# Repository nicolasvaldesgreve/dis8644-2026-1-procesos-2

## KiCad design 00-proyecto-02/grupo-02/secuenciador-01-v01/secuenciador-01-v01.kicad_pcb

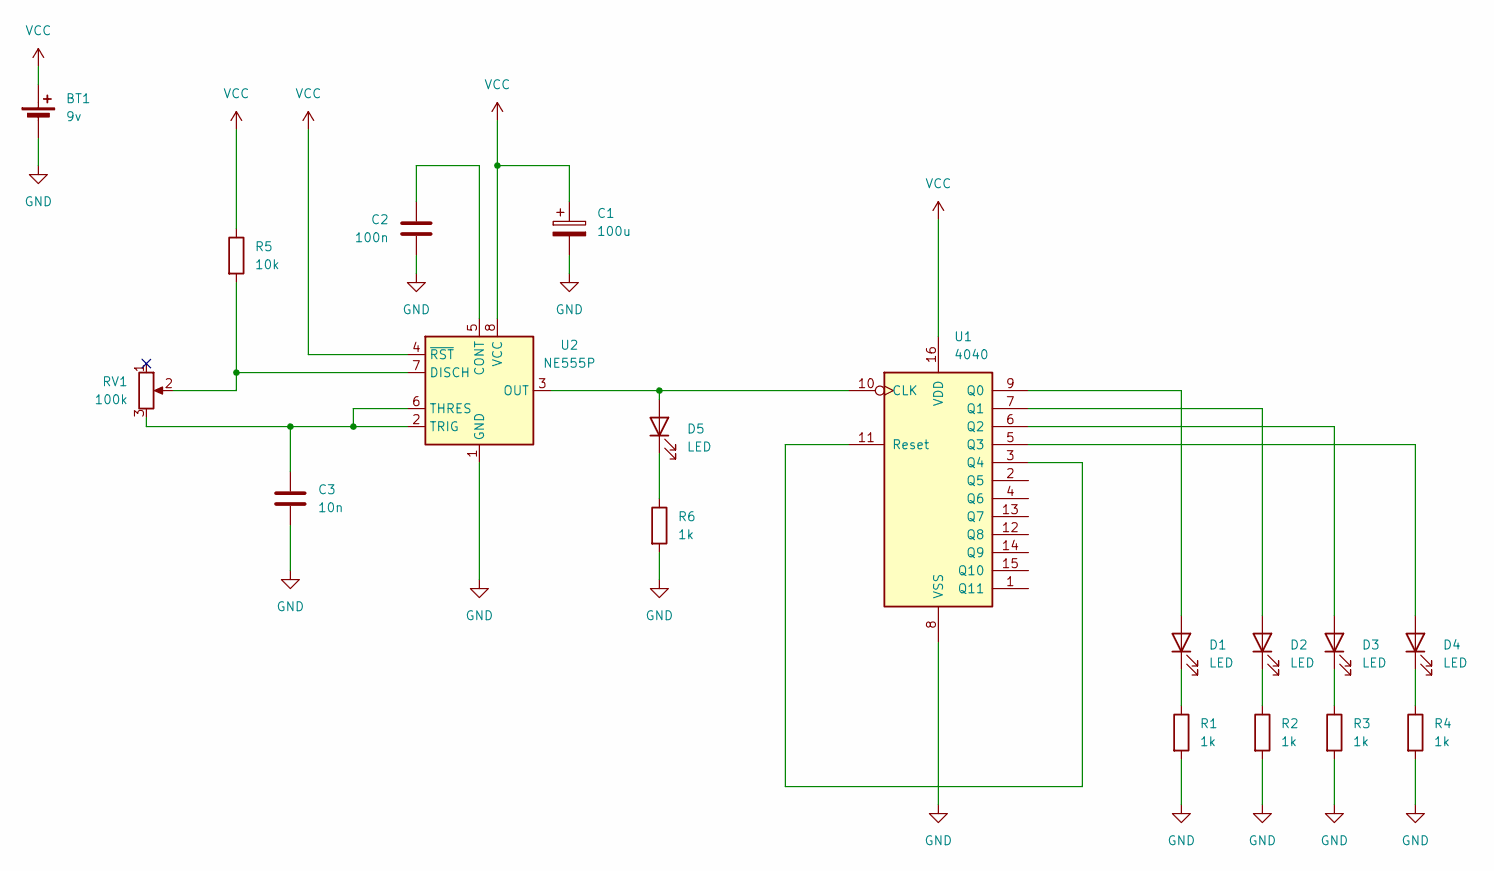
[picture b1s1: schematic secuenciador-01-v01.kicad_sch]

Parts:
BT1: 9v; TerminalBlock_MaiXu_MX126-5.0-02P_1x02_P5.00mm
C1: 100u; CP_Radial_D5.0mm_P2.50mm
C2: 100n; C_Disc_D3.8mm_W2.6mm_P2.50mm
C3: 10n; C_Disc_D3.8mm_W2.6mm_P2.50mm
D1, D2, D3, D4, D5: LED; LED_D5.0mm
R1, R2, R3, R4, R6: 1k; R_Axial_DIN0207_L6.3mm_D2.5mm_P10.16mm_Horizontal
R5: 10k; R_Axial_DIN0207_L6.3mm_D2.5mm_P10.16mm_Horizontal
RV1: 100k; Potentiometer_Alps_RK163_Single_Horizontal
U1: 4040; DIP-16_W7.62mm
U2: NE555P; DIP-8_W7.62mm

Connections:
GND: BT1.2 (-), C1.2, C2.2, C3.2, R1.2, R2.2, R3.2, R4.2, R6.2, U1.8 (VSS), U2.1 (GND)
unnamed: D1.2 (A), U1.9 (Q0)
unnamed: D1.1 (K), R1.1
unnamed: D2.2 (A), U1.7 (Q1)
unnamed: D2.1 (K), R2.1
unnamed: D3.2 (A), U1.6 (Q2)
unnamed: D3.1 (K), R3.1
unnamed: D4.2 (A), U1.5 (Q3)
unnamed: D4.1 (K), R4.1
unnamed: D5.2 (A), U1.10 (CLK), U2.3 (OUT)
unnamed: D5.1 (K), R6.1
unnamed: U1.3 (Q4), U1.11 (Reset)
unnamed: C2.1, U2.5 (CONT)
unnamed: R5.2, RV1.2, U2.7 (DISCH)
unnamed: C3.1, RV1.3, U2.2 (TRIG), U2.6 (THRES)
VCC: BT1.1 (+), C1.1, R5.1, U1.16 (VDD), U2.4 (~RST), U2.8 (VCC)

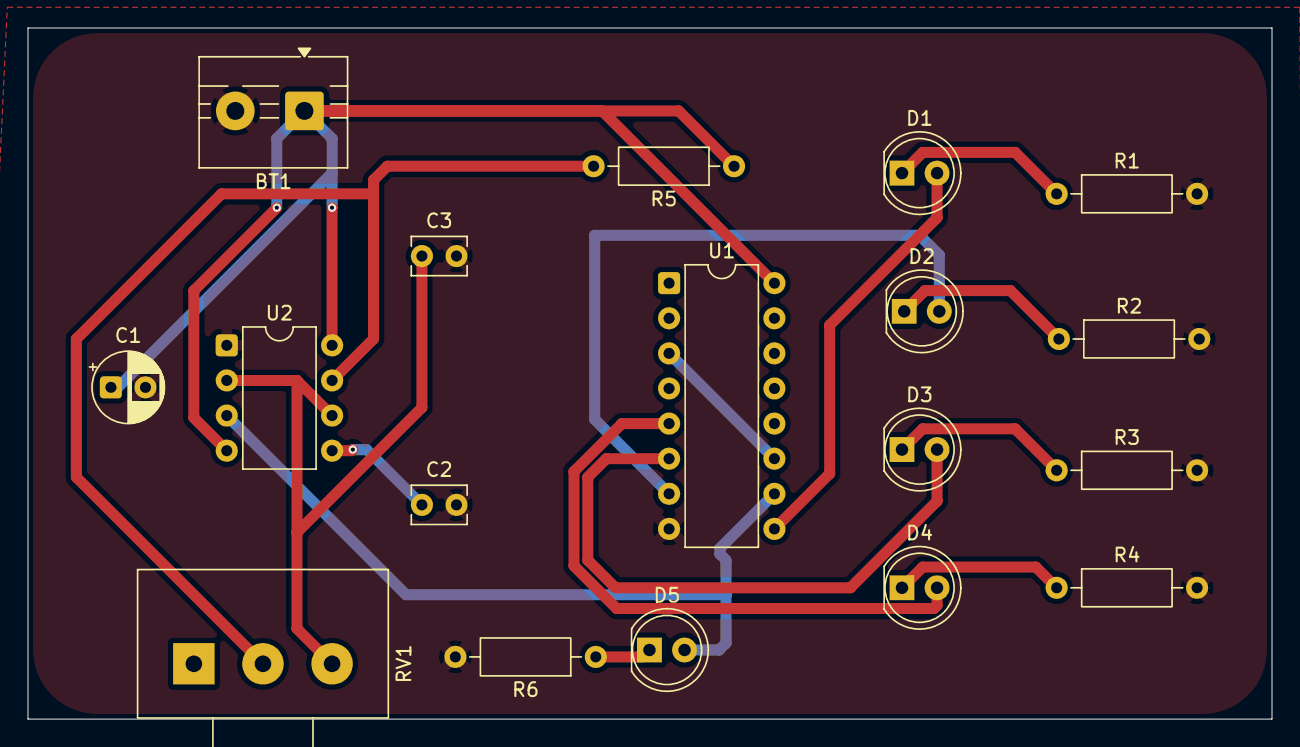
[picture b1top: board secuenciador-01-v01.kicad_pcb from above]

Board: 2 copper layers, 90.0 x 50.0 mm, 18 parts (0 on the bottom side), 16 nets.

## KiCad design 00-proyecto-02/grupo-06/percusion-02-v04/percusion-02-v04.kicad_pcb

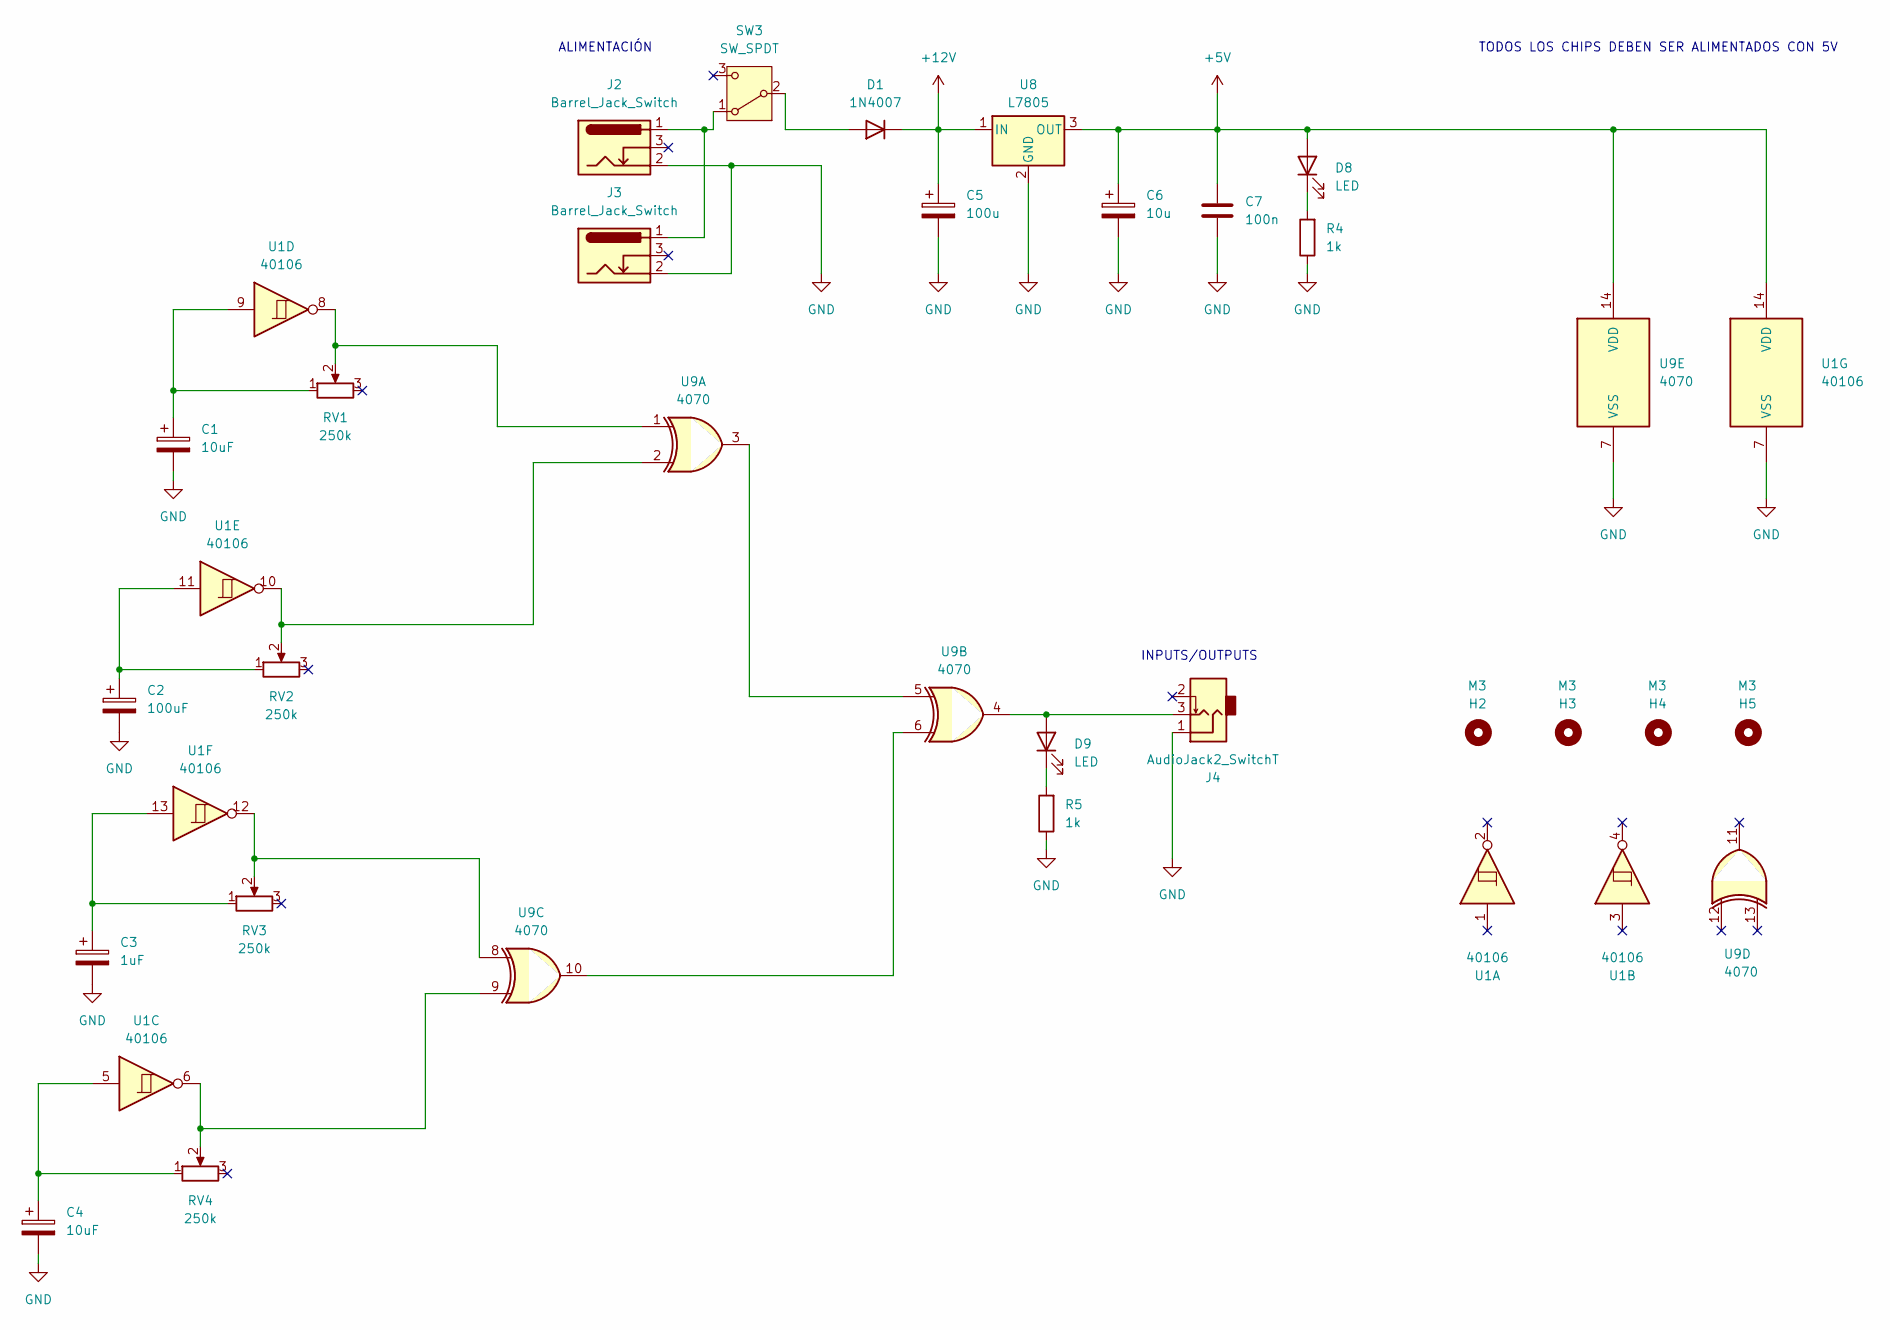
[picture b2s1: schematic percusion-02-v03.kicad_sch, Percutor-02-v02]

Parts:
C1, C4: 10uF; CP_Radial_D8.0mm_P3.80mm
C2: 100uF; CP_Radial_D8.0mm_P3.80mm
C3: 1uF; CP_Radial_D8.0mm_P3.80mm
C5: 100u; CP_Radial_D8.0mm_P3.80mm
C6: 10u; CP_Radial_D4.0mm_P2.00mm
C7: 100n; C_Disc_D5.0mm_W2.5mm_P2.50mm
D1: 1N4007; D_DO-41_SOD81_P10.16mm_Horizontal
D8, D9: LED; LED_D5.0mm
H2, H3, H4, H5: M3; MountingHole_3.2mm_M3
J2, J3: Barrel_Jack_Switch; BarrelJack_Horizontal
J4: AudioJack2_SwitchT; PJ301M-12
R4, R5: 1k; R_Axial_DIN0207_L6.3mm_D2.5mm_P10.16mm_Horizontal
RV1, RV2, RV3, RV4: 250k; Potentiometer_Alps_RK163_Single_Horizontal
SW3: SW_SPDT; spdt_ssd12d00g3
U1: 40106; DIP-14_W7.62mm_LongPads
U8: L7805; TO-220-3_Horizontal_TabDown
U9: 4070; DIP-14_W7.62mm_LongPads

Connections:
+5V: C6.1, C7.1, D8.2 (A), U1.14 (VDD), U8.3 (OUT), U9.14 (VDD)
+12V: C5.1, D1.1 (K), U8.1 (IN)
GND: C1.2, C2.2, C3.2, C4.2, C5.2, C6.2, C7.2, J2.2, J3.2, J4.1, R4.1, R5.1, U1.7 (VSS), U8.2 (GND), U9.7 (VSS)
unnamed: C1.1, RV1.1, U1.9
unnamed: C2.1, RV2.1, U1.11
unnamed: C3.1, RV3.1, U1.13
unnamed: C4.1, RV4.1, U1.5
unnamed: D1.2 (A), SW3.2 (B)
unnamed: D8.1 (K), R4.2
unnamed: D9.2 (A), J4.3, U9.4
unnamed: D9.1 (K), R5.2
unnamed: RV1.2, U1.8, U9.1
unnamed: RV2.2, U1.10, U9.2
unnamed: RV3.2, U1.12, U9.8
unnamed: RV4.2, U1.6, U9.9
unnamed: J2.1, J3.1, SW3.1 (A)
unnamed: U9.3, U9.5
unnamed: U9.6, U9.10

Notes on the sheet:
TODOS LOS CHIPS DEBEN SER ALIMENTADOS CON 5V
ALIMENTACIÓN
INPUTS/OUTPUTS

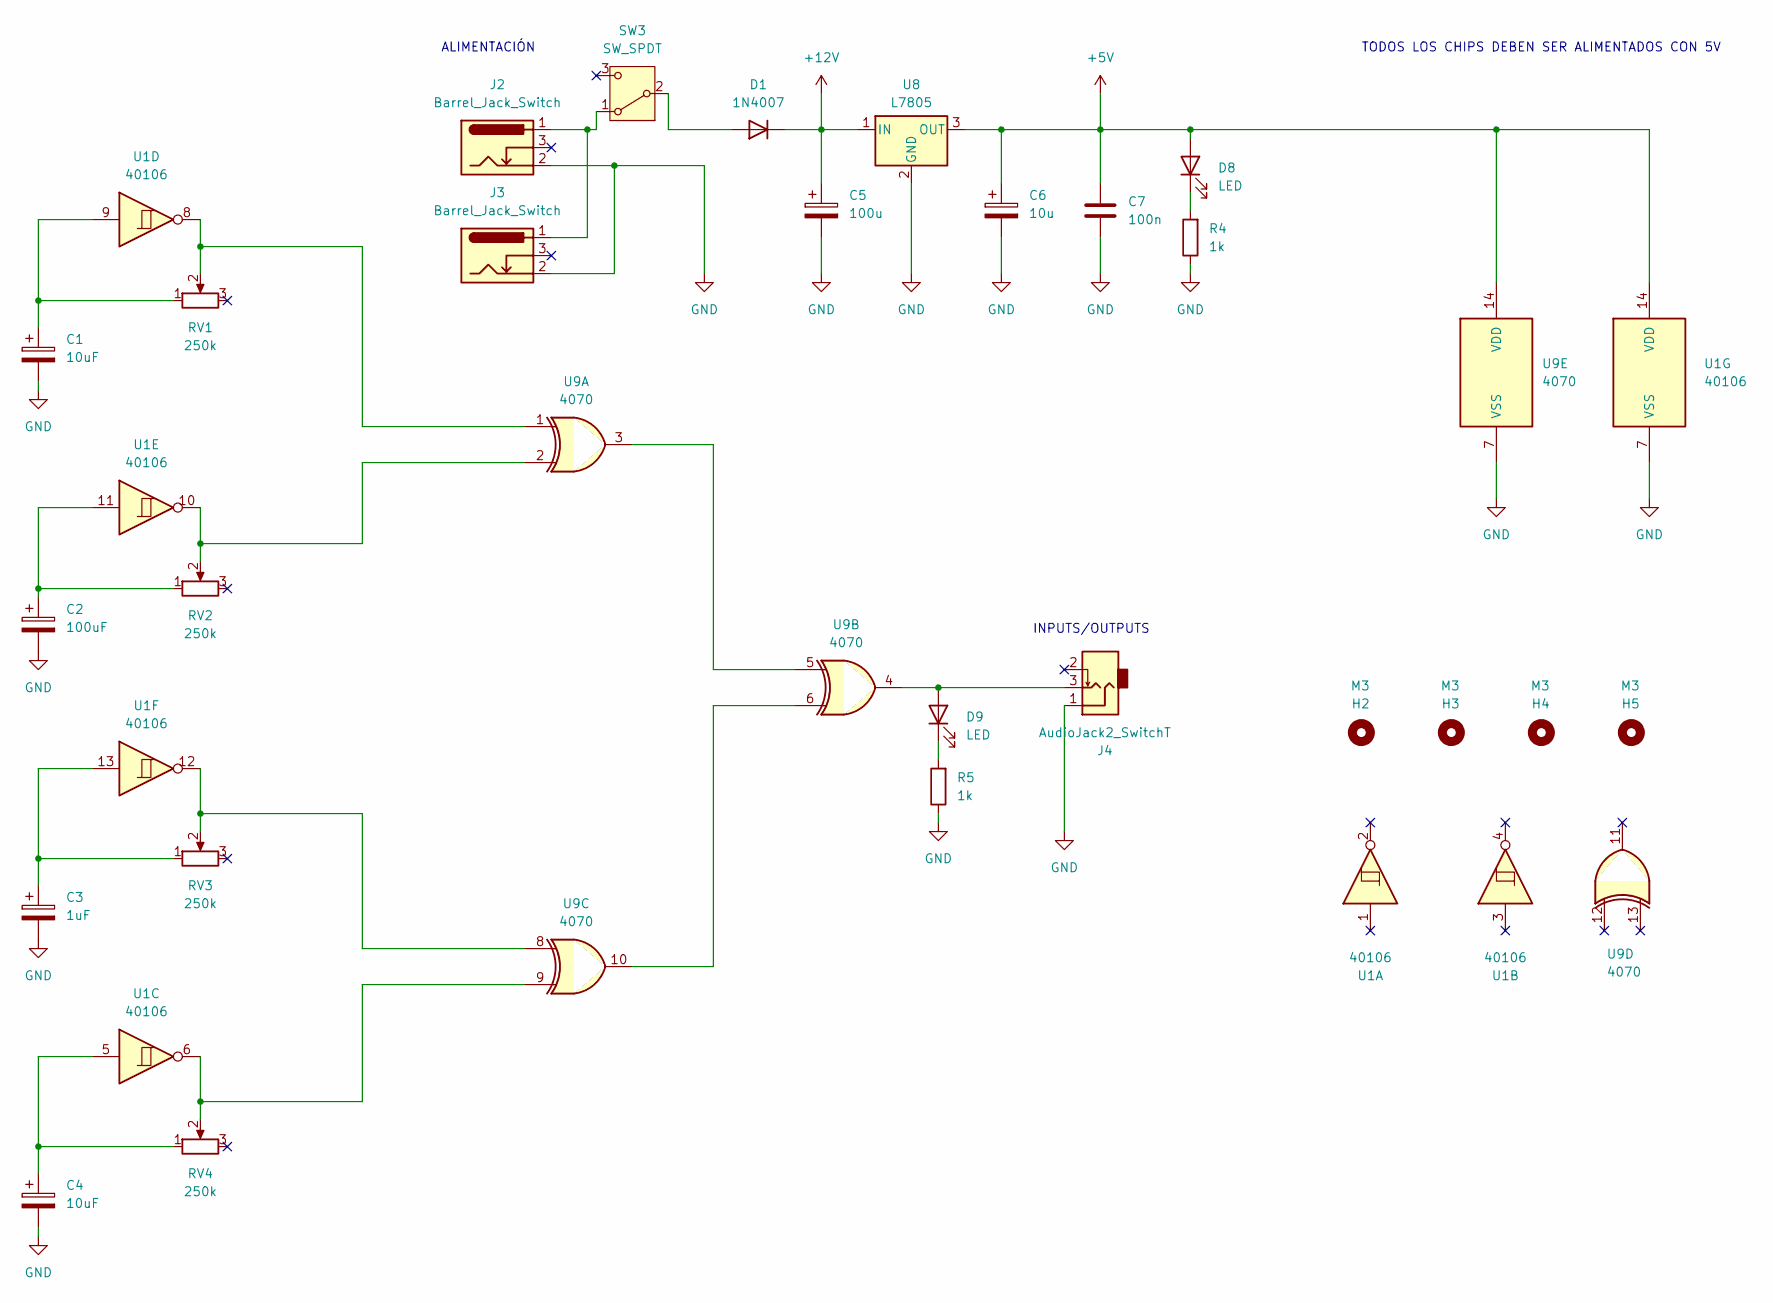
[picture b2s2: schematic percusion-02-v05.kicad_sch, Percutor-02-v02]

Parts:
C1, C4: 10uF; CP_Radial_D8.0mm_P3.80mm
C2: 100uF; CP_Radial_D8.0mm_P3.80mm
C3: 1uF; CP_Radial_D8.0mm_P3.80mm
C5: 100u; CP_Radial_D8.0mm_P3.80mm
C6: 10u; CP_Radial_D4.0mm_P2.00mm
C7: 100n; C_Disc_D5.0mm_W2.5mm_P2.50mm
D1: 1N4007; D_DO-41_SOD81_P10.16mm_Horizontal
D8, D9: LED; LED_D5.0mm
H2, H3, H4, H5: M3; MountingHole_3.2mm_M3
J2, J3: Barrel_Jack_Switch; BarrelJack_Horizontal
J4: AudioJack2_SwitchT; PJ301M-12
R4, R5: 1k; R_Axial_DIN0207_L6.3mm_D2.5mm_P10.16mm_Horizontal
RV1, RV2, RV3, RV4: 250k; Potentiometer_Alps_RK163_Single_Horizontal
SW3: SW_SPDT; spdt_ssd12d00g3
U1: 40106; DIP-14_W7.62mm_LongPads
U8: L7805; TO-220-3_Horizontal_TabDown
U9: 4070; DIP-14_W7.62mm_LongPads

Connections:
+5V: C6.1, C7.1, D8.2 (A), U1.14 (VDD), U8.3 (OUT), U9.14 (VDD)
+12V: C5.1, D1.1 (K), U8.1 (IN)
GND: C1.2, C2.2, C3.2, C4.2, C5.2, C6.2, C7.2, J2.2, J3.2, J4.1, R4.1, R5.1, U1.7 (VSS), U8.2 (GND), U9.7 (VSS)
unnamed: C1.1, RV1.1, U1.9
unnamed: C2.1, RV2.1, U1.11
unnamed: C3.1, RV3.1, U1.13
unnamed: C4.1, RV4.1, U1.5
unnamed: D1.2 (A), SW3.2 (B)
unnamed: D8.1 (K), R4.2
unnamed: D9.2 (A), J4.3, U9.4
unnamed: D9.1 (K), R5.2
unnamed: RV1.2, U1.8, U9.1
unnamed: RV2.2, U1.10, U9.2
unnamed: RV3.2, U1.12, U9.8
unnamed: RV4.2, U1.6, U9.9
unnamed: J2.1, J3.1, SW3.1 (A)
unnamed: U9.3, U9.5
unnamed: U9.6, U9.10

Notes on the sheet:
TODOS LOS CHIPS DEBEN SER ALIMENTADOS CON 5V
ALIMENTACIÓN
INPUTS/OUTPUTS

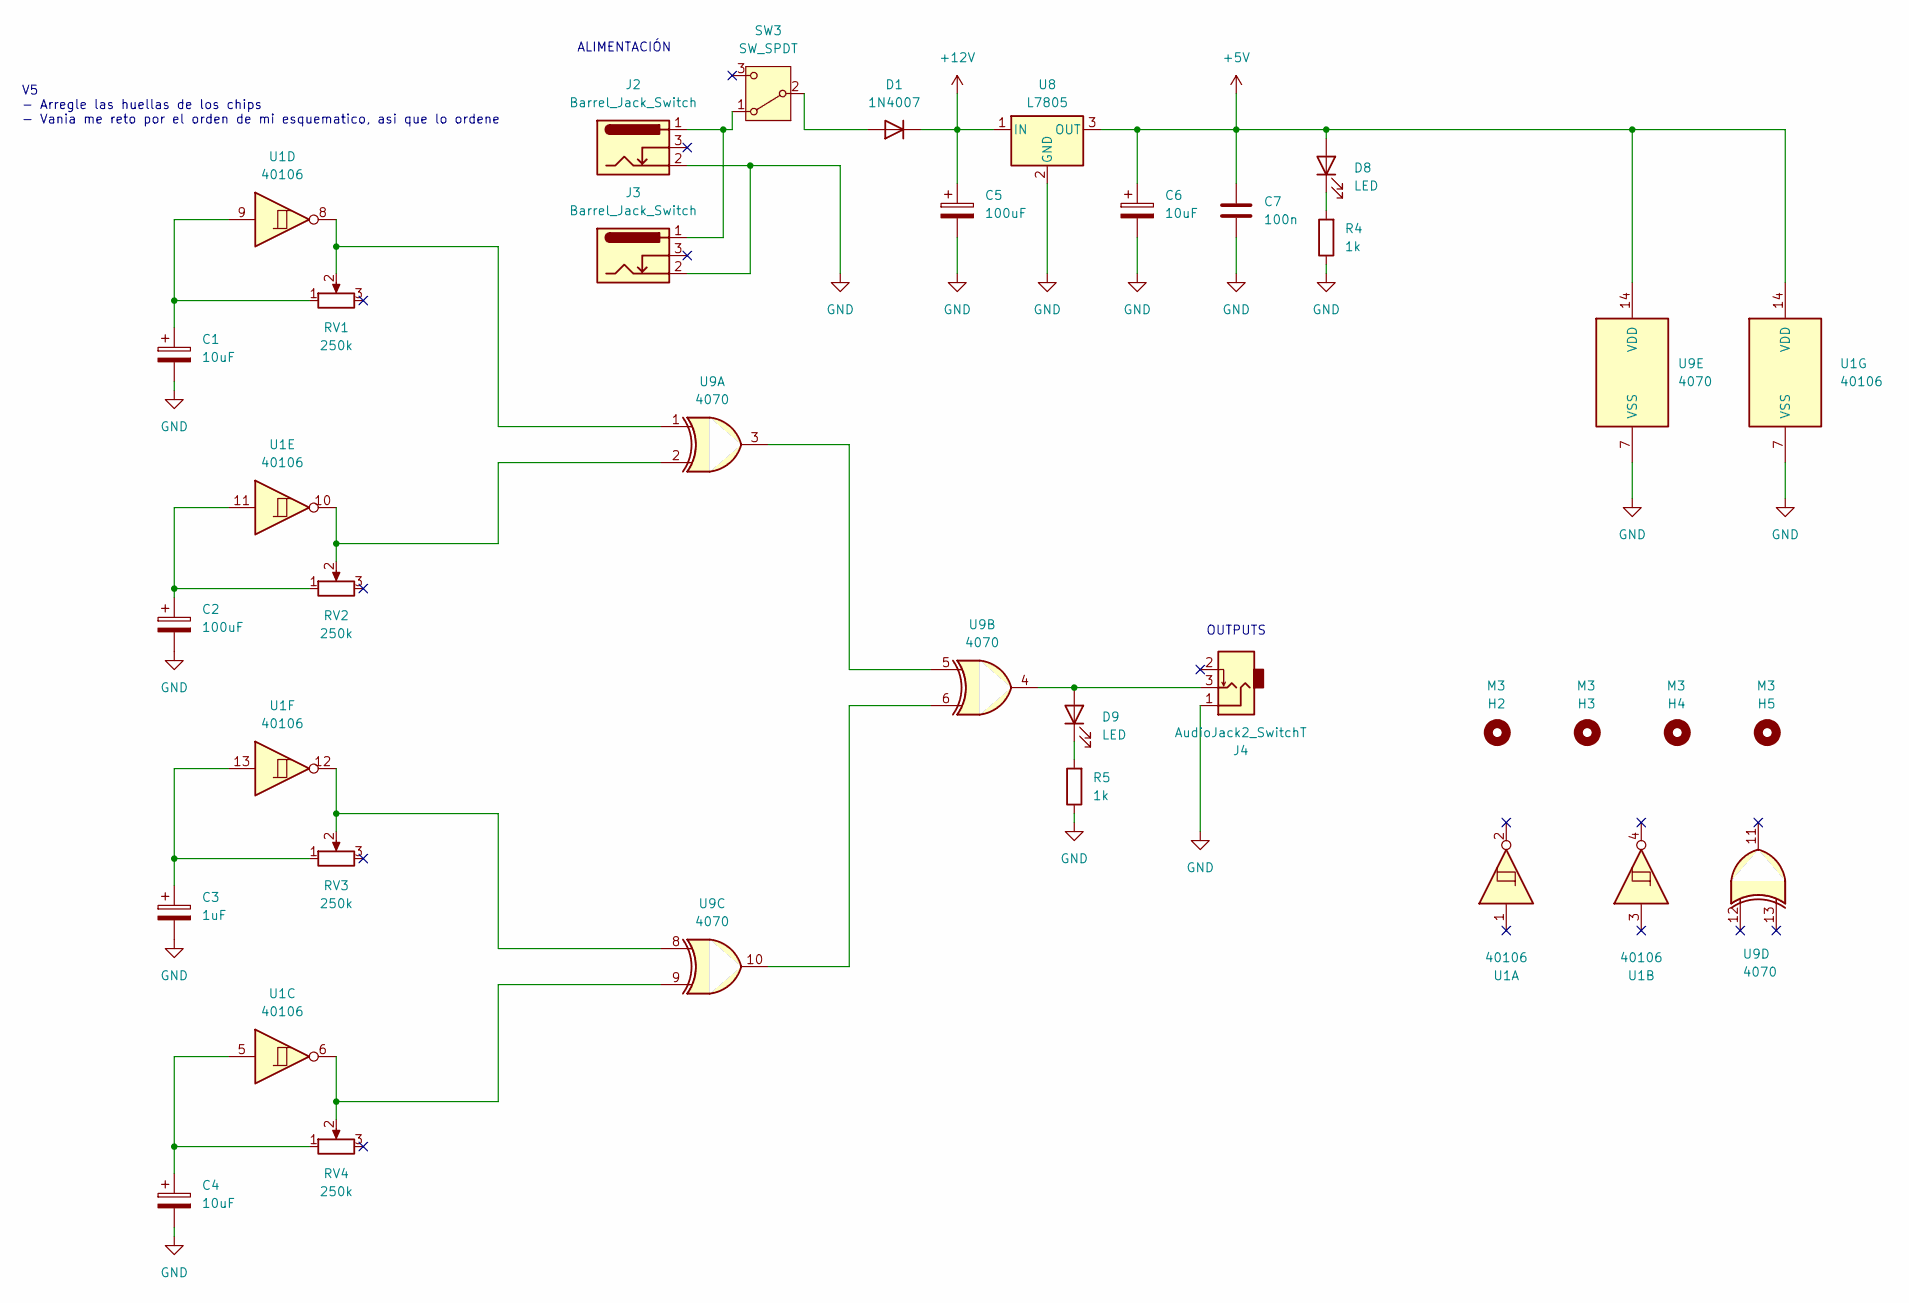
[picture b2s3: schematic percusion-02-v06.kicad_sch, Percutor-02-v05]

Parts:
C1, C4: 10uF; CP_Radial_D8.0mm_P3.80mm
C2, C5: 100uF; CP_Radial_D8.0mm_P3.80mm
C3: 1uF; CP_Radial_D8.0mm_P3.80mm
C6: 10uF; CP_Radial_D4.0mm_P2.00mm
C7: 100n; C_Disc_D5.0mm_W2.5mm_P2.50mm
D1: 1N4007; D_DO-41_SOD81_P10.16mm_Horizontal
D8, D9: LED; LED_D5.0mm
H2, H3, H4, H5: M3; MountingHole_3.2mm_M3
J2, J3: Barrel_Jack_Switch; BarrelJack_Horizontal
J4: AudioJack2_SwitchT; PJ301M-12
R4, R5: 1k; R_Axial_DIN0207_L6.3mm_D2.5mm_P10.16mm_Horizontal
RV1, RV2, RV3, RV4: 250k; Potentiometer_Alps_RK163_Single_Horizontal
SW3: SW_SPDT; spdt_ssd12d00g3
U1: 40106; DIP-14_W7.62mm_LongPads
U8: L7805; TO-220-3_Horizontal_TabDown
U9: 4070; DIP-14_W7.62mm_LongPads

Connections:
+5V: C6.1, C7.1, D8.2 (A), U1.14 (VDD), U8.3 (OUT), U9.14 (VDD)
+12V: C5.1, D1.1 (K), U8.1 (IN)
GND: C1.2, C2.2, C3.2, C4.2, C5.2, C6.2, C7.2, J2.2, J3.2, J4.1, R4.1, R5.1, U1.7 (VSS), U8.2 (GND), U9.7 (VSS)
unnamed: C1.1, RV1.1, U1.9
unnamed: C2.1, RV2.1, U1.11
unnamed: C3.1, RV3.1, U1.13
unnamed: C4.1, RV4.1, U1.5
unnamed: D1.2 (A), SW3.2 (B)
unnamed: D8.1 (K), R4.2
unnamed: D9.2 (A), J4.3, U9.4
unnamed: D9.1 (K), R5.2
unnamed: RV1.2, U1.8, U9.1
unnamed: RV2.2, U1.10, U9.2
unnamed: RV3.2, U1.12, U9.8
unnamed: RV4.2, U1.6, U9.9
unnamed: J2.1, J3.1, SW3.1 (A)
unnamed: U9.3, U9.5
unnamed: U9.6, U9.10

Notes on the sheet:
ALIMENTACIÓN
OUTPUTS
V5 - Arregle las huellas de los chips - Vania me reto por el orden de mi esquematico, asi que lo ordene

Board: 2 copper layers, 26 parts (4 on the bottom side), 18 nets, no tracks yet.
